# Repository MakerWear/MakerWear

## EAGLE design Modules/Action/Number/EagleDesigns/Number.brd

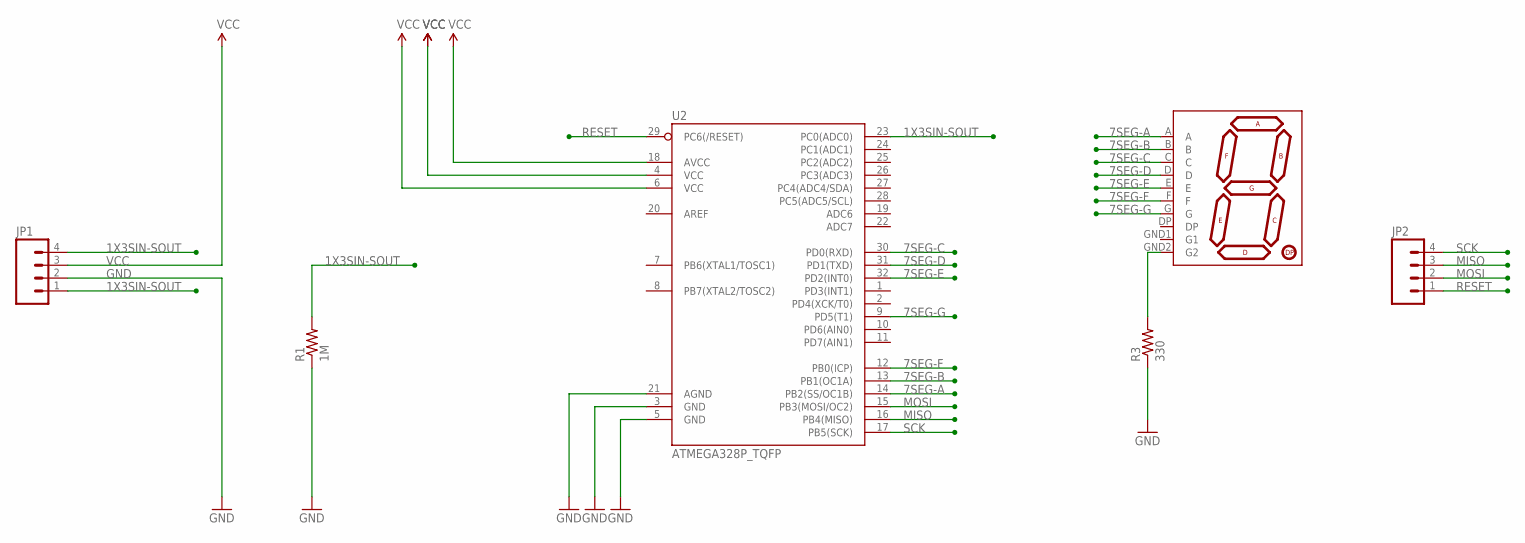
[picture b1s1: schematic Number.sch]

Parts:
JP1, JP2: M04PTH; 1X04
R1: 1M; R0603
R3: 330; R0603
U2: ATMEGA328P_TQFP; TQFP32-08
U$1: 7SEGMENT; 7SEG-SMD-10X7.3

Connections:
1X3SIN-SOUT: JP1.1, JP1.4, R1.2, U2.23 (PC0(ADC0))
7SEG-A: U2.14 (PB2(SS/OC1B)), U$1.A
7SEG-B: U2.13 (PB1(OC1A)), U$1.B
7SEG-C: U2.30 (PD0(RXD)), U$1.C
7SEG-D: U2.31 (PD1(TXD)), U$1.D
7SEG-E: U2.32 (PD2(INT0)), U$1.E
7SEG-F: U2.12 (PB0(ICP)), U$1.F
7SEG-G: U2.9 (PD5(T1)), U$1.G
GND: JP1.2, R1.1, R3.1, U2.3 (GND), U2.5 (GND), U2.21 (AGND)
MISO: JP2.3, U2.16 (PB4(MISO))
MOSI: JP2.2, U2.15 (PB3(MOSI/OC2))
unnamed: R3.2, U$1.GND2 (G2)
RESET: JP2.1, U2.29 (PC6(/RESET))
SCK: JP2.4, U2.17 (PB5(SCK))
VCC: JP1.3, U2.4 (VCC), U2.6 (VCC), U2.18 (AVCC)

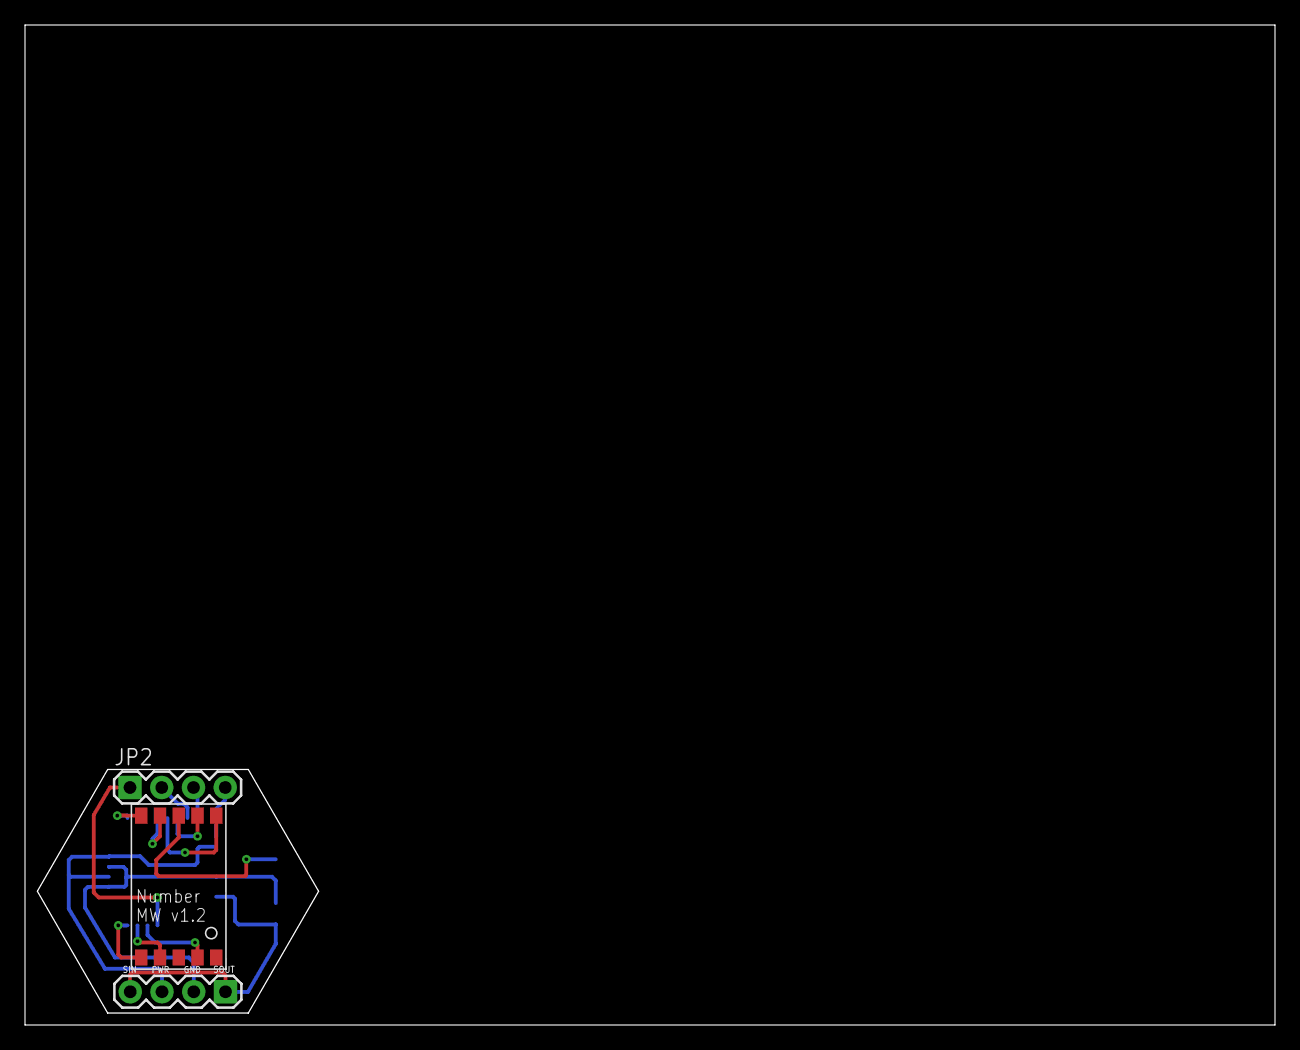
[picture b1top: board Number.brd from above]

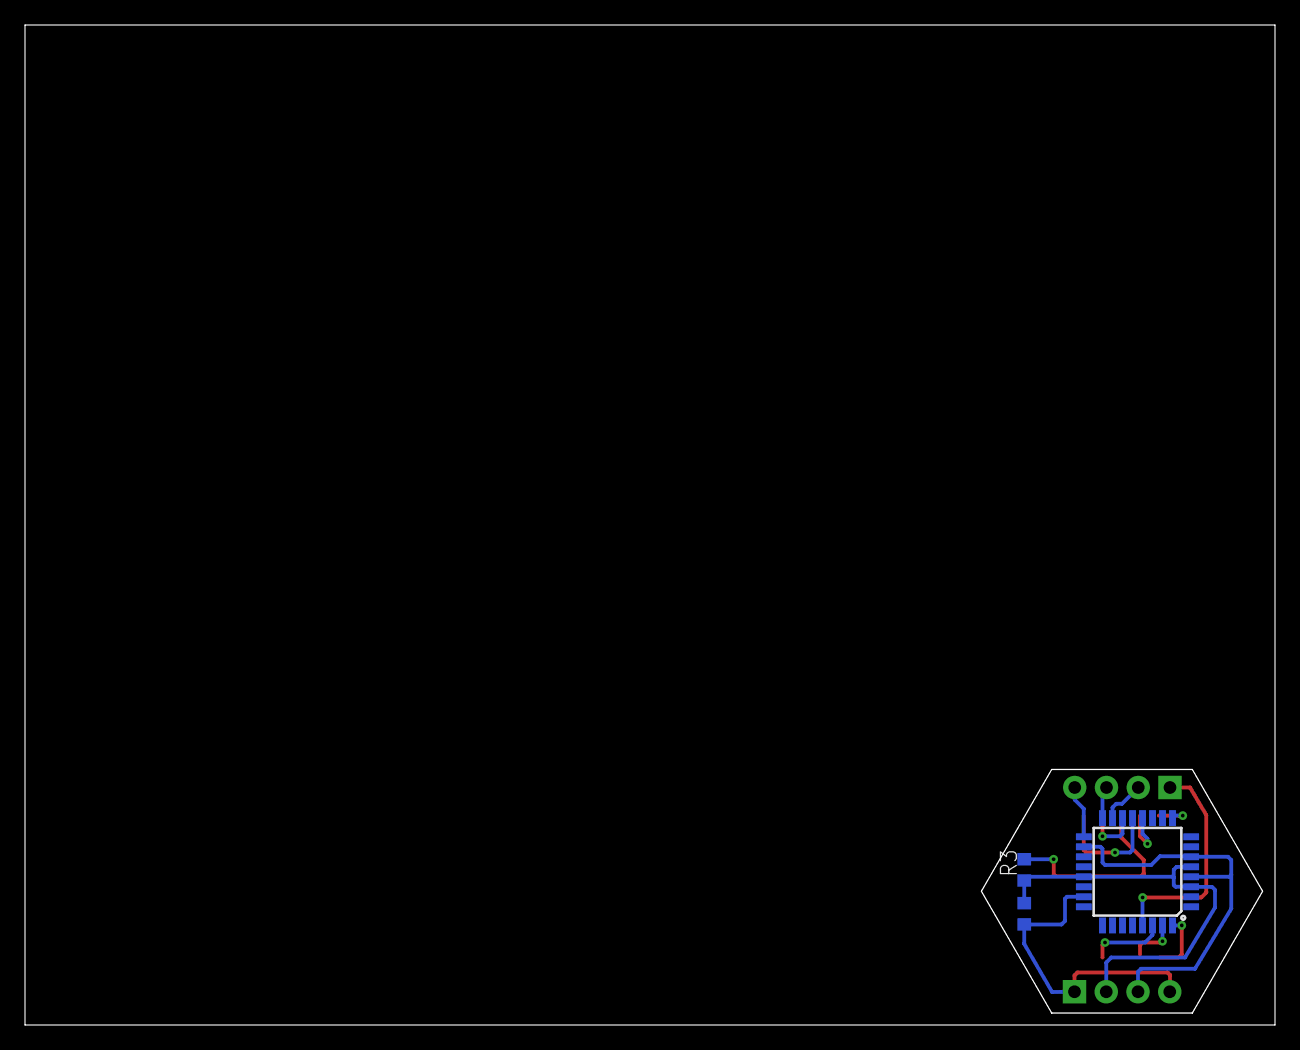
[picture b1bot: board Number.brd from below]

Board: 2 copper layers, 100.0 x 80.0 mm, 6 parts (3 on the bottom side), 15 nets.

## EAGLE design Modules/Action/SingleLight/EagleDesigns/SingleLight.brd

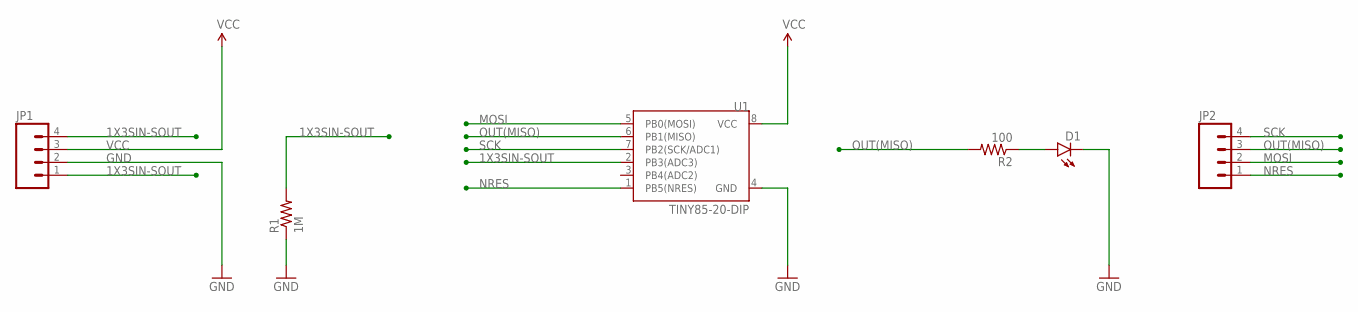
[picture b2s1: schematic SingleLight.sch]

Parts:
D1: LED5MM
JP1, JP2: M04PTH; 1X04
R1: 1M; R0603
R2: 100; R0603
U1: TINY85-20-DIP; DIP08

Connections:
1X3SIN-SOUT: JP1.1, JP1.4, R1.2, U1.2 (PB3(ADC3))
GND: D1.K (C), JP1.2, R1.1, U1.4 (GND)
MOSI: JP2.2, U1.5 (PB0(MOSI))
unnamed: D1.A, R2.1
NRES: JP2.1, U1.1 (PB5(NRES))
OUT(MISO): JP2.3, R2.2, U1.6 (PB1(MISO))
SCK: JP2.4, U1.7 (PB2(SCK/ADC1))
VCC: JP1.3, U1.8 (VCC)

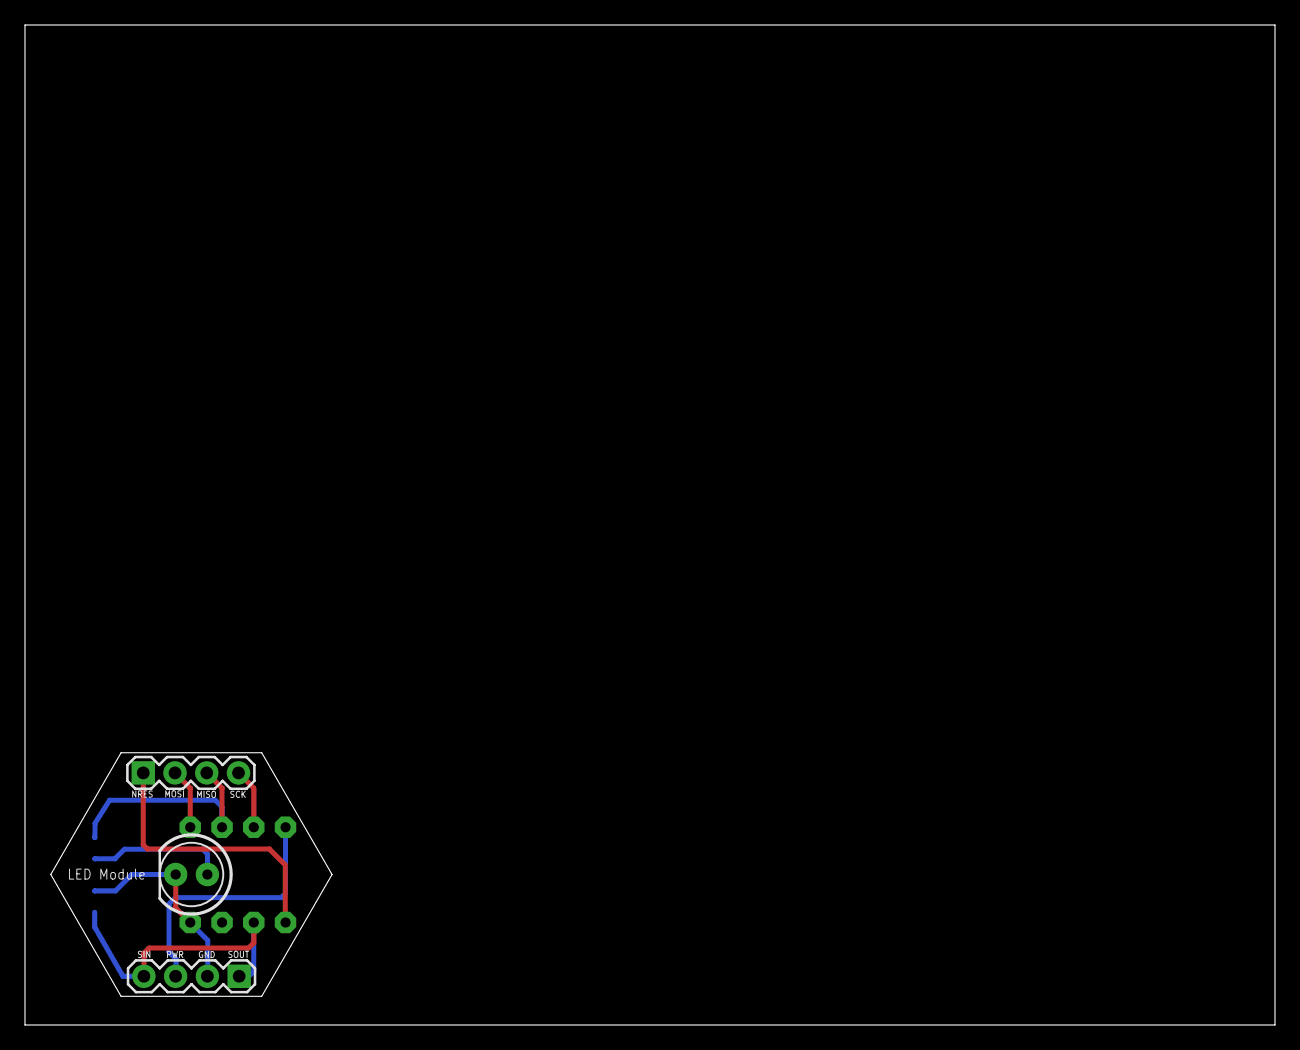
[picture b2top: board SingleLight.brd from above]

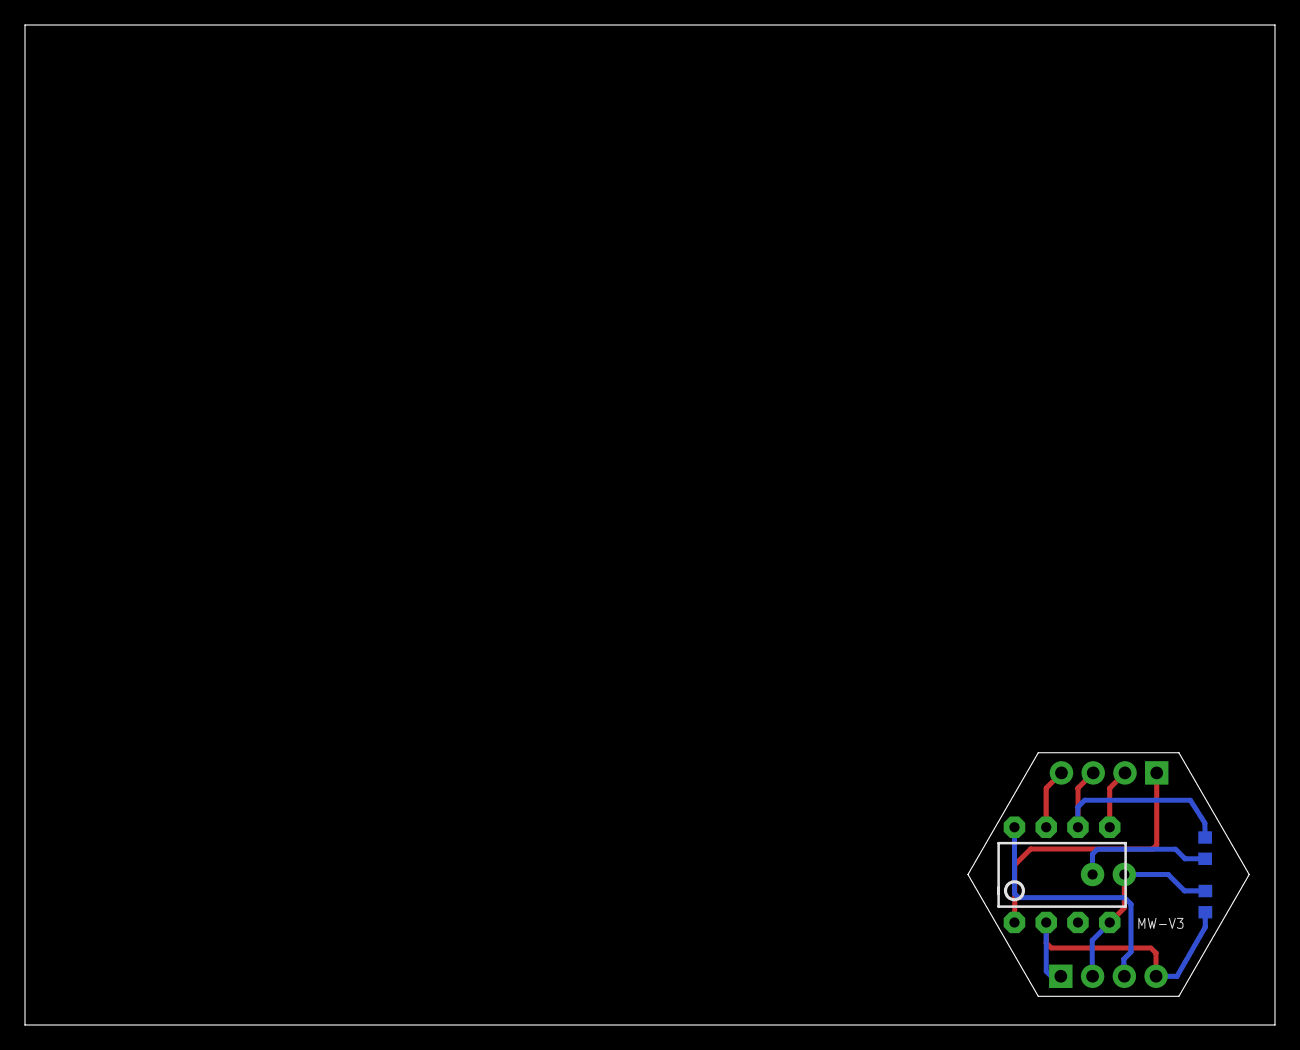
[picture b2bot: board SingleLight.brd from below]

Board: 2 copper layers, 100.0 x 80.0 mm, 6 parts (3 on the bottom side), 8 nets.

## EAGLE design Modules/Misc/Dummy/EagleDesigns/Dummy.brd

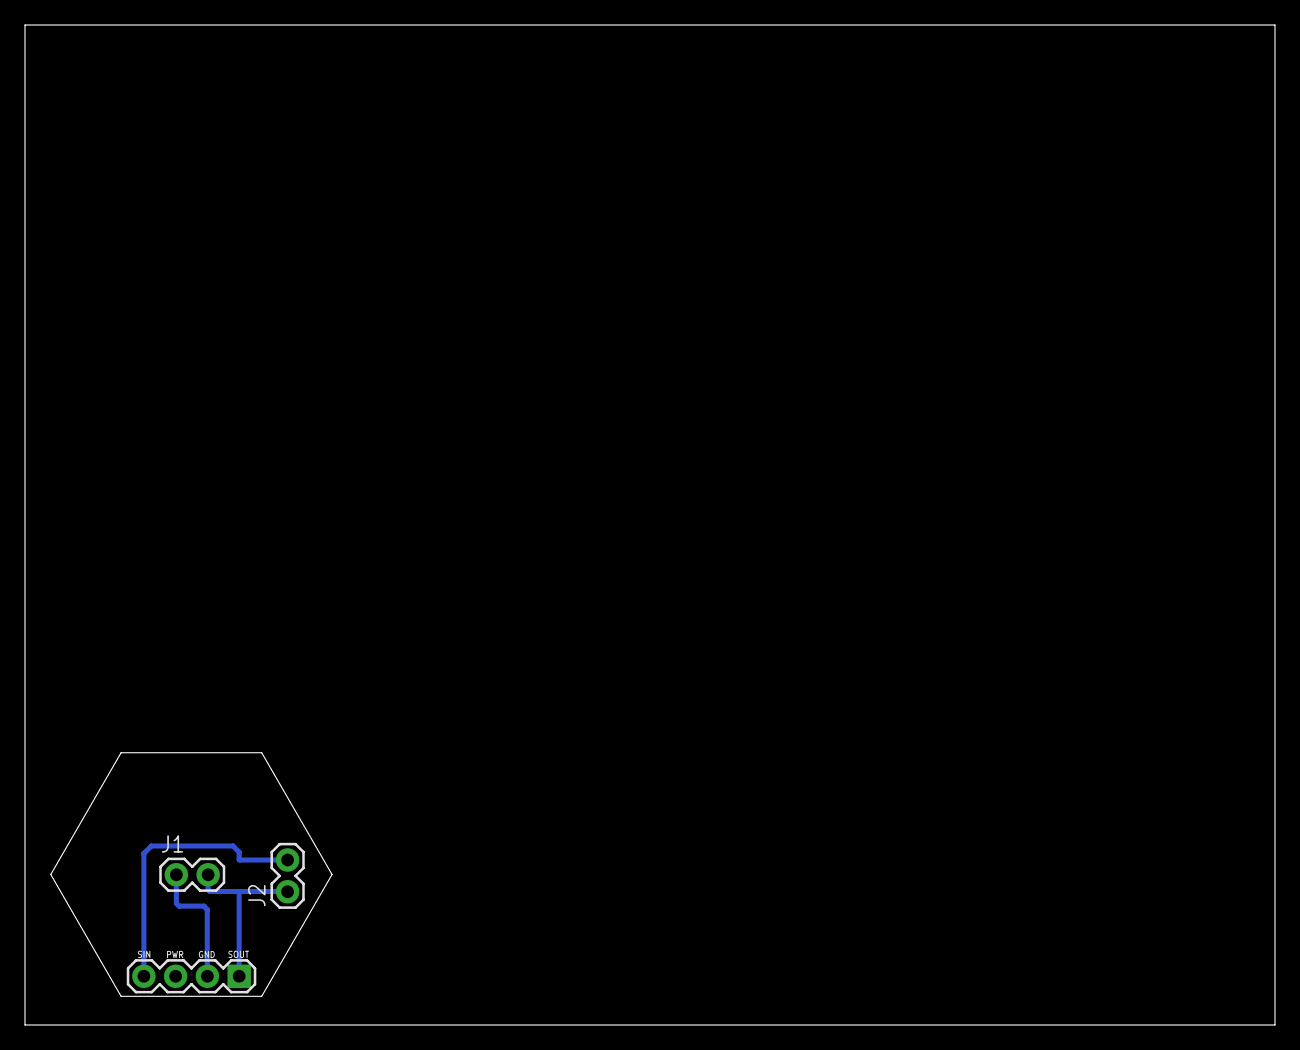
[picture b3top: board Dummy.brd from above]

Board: 2 copper layers, 100.0 x 80.0 mm, 3 parts (0 on the bottom side), 3 nets.

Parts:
J1, J2: 1X02
JP1: 1X04

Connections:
GND: J1.1, JP1.2
SIN: J2.2, JP1.4
SOUT: J1.2, J2.1, JP1.1

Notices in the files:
parts and their libraries:
SparkFun-Connectors: Licensing: Creative Commons ShareAlike 4.0 International - https://creativecommons.org/licenses/by-sa/4.0
